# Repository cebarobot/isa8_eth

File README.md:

# ISA 8-Bit Ethernet Controller (THT Version)
ISA 8-Bit Ethernet Network Interface Controller (THT Version)

This is a modified version of [Sergey Kiselev's ISA 8-Bit Ethernet Controller](https://github.com/skiselev/isa8_eth), where surface-mount (SMD) components, except for the RTL8019AS, have been replaced with through-hole (THT) components.

## Changes
* Surface-mount (SMD) components, except for the RTL8019AS, have been replaced with through-hole (THT) components.
* Ethernet Jack (Amphenol RJMG1BD3B8K1ANR) has been replaced by HanRun HR911105A.
* Circuit layout and silkscreen.

## Introduction
ISA 8-Bit Ethernet Controller is an open source network interface controller (NIC) card, designed specifically to be used in computers with 8-bit only ISA (aka XT) bus, such as IBM* PC, IBM* PC XT, various PC/XT compatibles, for example [Micro 8088](https://github.com/skiselev/micro_8088) system. It is based on Realtek RTL8019 ethernet controller and is NE2000-compatible.

## Specifications
* ISA 8-bit interface (62 pin / card edge)
* NE2000 compatible
  * Note: Popular Crynwr NE2000 pocket driver does not support NE2000 in 8-bit slots. Please use the [patched driver](software/driver/) instead
* Supports configuration using switches, jumperless configuration using [RSET8019](software/RSET8019/) utility or PnP
  * Uses DIP switches instead of jumpers for reliability and ease of configuration
* Boot ROM support
  * Socket supports 512 KiB Flash ROM, such as SST/Microchip 39SF040
  * Can be configured in 16 KiB, 32 KiB, 64 KiB, or page mode. In page mode the entire 512 KiB are accessible through a 16 KiB window
  * Also compatible with other DIP 32-pin Flash ROMs, such as 128 KiB 39SF010A, and 256 KiB 39SF020, or similar
  * 40-pin memory extension connector allows connecting up to 4 MiB of memory that can be used in page mode

## Hardware Documentation

### Schematic and PCB Layout

[Schematic - Version THT 1.1](KiCad/ISA8_Ethernet-Schematic-THT-1.1.pdf)

[PCB Layout - Version THT 1.1](KiCad/ISA8_Ethernet-Board-THT-1.1.pdf)

### Building Instructions

#### Assemble the PCB

* Clean the PCB with alcohol
* Apply fluid flux to SMD components pads
* Solder U1 RTL8019 IC
* Solder R1 - R7 resistors and RN1 - RN4 resistor arrays
  * Note that RN1 - RN3 are only required if using DIP switches for configuration. They are not required for jumperless configuration
* Solder C1 - C8 ceramic capacitors
* Solder C9 and C10 tantalum capacitors
* Solder Y1 crystal
* Optional: Program U3 EEPROM. Make sure to use unique MAC address
  * Note: EEPROM can be programmed later using [PG8019](software/PG8019/) utility
* Solder U3 EEPROM
* Optional: Solder SW1 - SW4 DIP switches and U2 IC socket
* Solder J1 Ethernet jack with integrated magentics
* Clean the remaining flux with alcohol

#### Program EEPROM

If EEPROM has not been programmed prior to assembly, now it is a good time to do so.
The U3 EEPROM contains the following configuration for the RTL8019AS chip:
* MAC address
* ISA resources for jumperless configuration
  * Base I/O address
  * IRQ number
  * Boot ROM mode, size, and base memory address
* Other ethernet controller confirguration - medium type, full duplex, LEDs function, power management settings
* Product ID (not normally used, although some vendor specific drivers might check for it)
* Plug and Play data
  * Vendor ID, serial number, PnP version, I/O, memory, and IRQ resources

This information can be programmed using [PG8019](software/PG8019/) utility. The 8019AS.CFG file contains the recommended configuration. Make sure to edit it, and update the MAC address and the serial number. Note that the MAC address is given in the Big-endian format (that is the last byte has the least significant value), while the serial number is given in Little-endian format (that is the first byte has the least significant value). 

A few notes about using PG8019:
* Make sure that your system has 0x300-0x31F I/O addresses available regardless of the Ethernet controller addresses specified in 8019AS.CFG. Note that XT-IDE and XT-CF-Lite frequently use this I/O range. In case you have such a card, you can either temporarily remove it from your system, boot and run PG8019 from a floppy disk, or switch your XT-IDE or XT-CF-Lite to a different address. In the latter case you'll need to update the XT IDE BIOS configuration
* Make sure that your system boots in real mode (no EMM386), or anything else that might interfer with the card. Ideally boot your system without any drivers loaded at all, for example, in later MS-DOS versions it is possible to bypass CONFIG.SYS and AUTOEXEC.BAT by hitting F5 key at the boot time
* After EEPROM has been programmed successfully, the PG8019 utility will print the MAC address, also, it will automatically increment the MAC address and the serial number in 8019AS.CFG, which is useful when programming multiple cards

[Openmoko Inc.](https://github.com/skiselev/openmoko-usb-oui) has generously allocated [00-1F-11-02-60-00 - 00-1F-11-02-7F-FF](https://github.com/skiselev/openmoko-usb-oui/blob/master/ieee_oui.psv) MAC addresses range for ISA 8-Bit Ethernet controller project. You can use MAC addresses from this range for your build, as long as you are using this design. Please apply for a different range if you're redesigning the board or re-using this Ethernet controller design in your own project. I ask you not to use 00-1F-11-02-60-00 - 00-1F-11-02-63-FF range (first 1024 addresses). I am using this range for the cards that I build.

#### Test Ethernet Controller

* Connect Ethernet cable. Make sure that the green "Link" LED lights up
* Use mTCP to test the controller
  * DHCP to obtain IP address
  * FTP or HTGET to download a file

### Switches and Connectors

#### SW1 - CONFIG
This switch block sets the configuration mode

Configuration Mode    | Switch Position
--------------------- | ------------------------
Jumperless / RSET8019 | SW1.1 = OFF, SW1.2 = OFF
Switches              | SW1.1 = ON, SW1.2 = OFF
PnP                   | SW1.1 = OFF, SW1.2 = ON

#### SW2 - IRQ
This switch block, when the card is in the **Switches** configuration mode, sets the Ethernet controller IRQ

IRQ                             | Switch Position
------------------------------- | ------------------------
IRQ2 (on PC/XT) or IRQ9 (on AT) | SW2.1 = OFF, SW2.2 = OFF
IRQ3                            | SW2.1 = ON, SW2.2 = OFF
IRQ4                            | SW2.1 = OFF, SW2.2 = ON
IRQ5                            | SW2.1 = ON, SW2.2 = ON

#### SW3 - IO_ADDR
This switch block, when the card is in the **Switches** configuration mode, sets the Ethernet controller I/O address

I/O Address | SW3.1 | SW3.2 | SW3.3 | SW3.4
----------- | ----- | ----- | ------| -----
0x200       | OFF   | OFF   | ON    | OFF
0x220       | ON    | OFF   | ON    | OFF
0x240       | OFF   | ON    | ON    | OFF
0x260       | ON    | ON    | ON    | OFF
0x280       | OFF   | OFF   | ON    | ON
0x2A0       | ON    | OFF   | ON    | ON
0x2C0       | OFF   | ON    | ON    | ON
0x2E0       | ON    | ON    | ON    | ON
0x300       | OFF   | OFF   | OFF   | OFF
0x320       | ON    | OFF   | OFF   | OFF
0x340       | OFF   | ON    | OFF   | OFF
0x360       | ON    | ON    | OFF   | OFF
0x380       | OFF   | OFF   | OFF   | ON
0x3A0       | ON    | OFF   | OFF   | ON
0x3C0       | OFF   | ON    | OFF   | ON
0x3E0       | ON    | ON    | OFF   | ON

#### SW4 - ROM_ADDR
This switch block, when the card is in the **Switches** configuration mode, sets the Ethernet controller boot ROM address and size

ROM Address  | ROM Size           | SW4.1 | SW4.2 | SW4.3 | SW4.4 | SW4.5
------------ | ------------------ | ----- | ------| ----- | ----- | -----
ROM Disabled | Not applicable     | *     | *     | *     | OFF   | OFF
0xC0000      | 16 KiB             | OFF   | OFF   | OFF   | OFF   | ON
0xC4000      | 16 KiB             | ON    | OFF   | OFF   | OFF   | ON
0xC8000      | 16 KiB             | OFF   | ON    | OFF   | OFF   | ON
0xCC000      | 16 KiB             | ON    | ON    | OFF   | OFF   | ON
0xD0000      | 16 KiB             | OFF   | OFF   | ON    | OFF   | ON
0xD4000      | 16 KiB             | ON    | OFF   | ON    | OFF   | ON
0xD8000      | 16 KiB             | OFF   | ON    | ON    | OFF   | ON
0xDC000      | 16 KiB             | ON    | ON    | ON    | OFF   | ON
0xC0000      | 32 KiB             | OFF   | OFF   | OFF   | ON    | OFF
0xC8000      | 32 KiB             | ON    | OFF   | OFF   | ON    | OFF
0xD0000      | 32 KiB             | OFF   | ON    | OFF   | ON    | OFF
0xD8000      | 32 KiB             | ON    | ON    | OFF   | ON    | OFF
0xC0000      | 64 KiB             | OFF   | OFF   | ON    | ON    | OFF
0xD0000      | 64 KiB             | ON    | OFF   | ON    | ON    | OFF
0xC0000      | 16 KiB / Page mode | OFF   | OFF   | OFF   | ON    | ON
0xC4000      | 16 KiB / Page mode | ON    | OFF   | OFF   | ON    | ON
0xC8000      | 16 KiB / Page mode | OFF   | ON    | OFF   | ON    | ON
0xCC000      | 16 KiB / Page mode | ON    | ON    | OFF   | ON    | ON
0xD0000      | 16 KiB / Page mode | OFF   | OFF   | ON    | ON    | ON
0xD4000      | 16 KiB / Page mode | ON    | OFF   | ON    | ON    | ON
0xD8000      | 16 KiB / Page mode | OFF   | ON    | ON    | ON    | ON
0xDC000      | 16 KiB / Page mode | ON    | ON    | ON    | ON    | ON

#### J1 - Ethernet Connector

#### J2 - MEM_EXT
This connector can be used to add up to 4 MiB of optional memory (ROM or RAM).
The memory, if larger than 64 KiB, can be accessed using the page mode.

Pin | Description   | Pin | Description
--- | ------------- | --- | -----------
1   | 5V            | 2   | 5V
3   | No connection | 4   | A21
5   | No connection | 6   | A20
7   | No connection | 8   | A19
9   | A18           | 10  | /MEMW
11  | A16           | 12  | A17
13  | A15           | 14  | A14
15  | A12           | 16  | A13
17  | A7            | 18  | A8
19  | A6            | 20  | A9
21  | A5            | 22  | A11
23  | A4            | 24  | /MEMR
25  | A3            | 26  | A10
27  | A2            | 28  | /CS
29  | A1            | 30  | D7
31  | A0            | 32  | D6
33  | D0            | 34  | D5
35  | D1            | 36  | D4
37  | D2            | 38  | D3
39  | GND           | 40  | GND

### Bill of Materials - Version THT 1.1

Component type     | Reference | Description                           | Quantity | Possible sources and notes 
------------------ | --------- | ------------------------------------- | -------- | --------------------------
PCB                |           | ISA 8-bit Ethernet PCB - Version 1.0  | 1        | Order from a PCB manufacturer of your choice using provided Gerber or KiCad files
Integrated Circuit | U1        | Realtek RTL8019AS Ethernet Controller | 1        | Authorized Realtek distributors or Taobao
Integrated Circuit | U2        | SST39SF040 - 512 KiB Flash ROM, 32 pin DIP  | 1  | Optional - Boot ROM. 
Integrated Circuit | U3        | 93C46 - 1 Kbit EEPROM, 8 pin DIP      | 1        | Taobao
Quartz Crystal     | Y1        | 20 MHz, 20pF, HC-49U                  | 1        | Taobao
Ethernet Jack      | J1        | HanRun HR911105A - Ethernet jack with magnetics | 1 | Taobao
DIP Switch         | SW1, SW2  | DIP switch, 2 position, SPST          | 2        | Taobao
DIP Switch         | SW3       | DIP switch, 4 position, SPST          | 1        | Taobao
DIP Switch         | SW4       | DIP switch, 5 position, SPST          | 1        | Taobao
Capacitor          | C1, C2    | 30pF MLCC Capacitor, 5.08 mm pitch    | 2        | Taobao
Capacitor          | C3, C4    | 0.01uF MLCC Capacitor, 5.08 mm pitch  | 2        | Taobao
Capacitor          | C5 - C8   | 0.1uF MLCC Capacitor, 5.08 mm pitch   | 4        | Taobao
Capacitor          | C1, C2    | 22uF Tantalum Capacitor, 2.54 mm pitch| 2        | Taobao
Resistor           | R1        | 200 Ohm Resistor, 1/4W, through hole  | 1        | Taobao
Resistor           | R2, R3    | 470 Ohm Resistor, 1/4W, through hole  | 2        | Taobao
Resistor           | R6        | 27 kOhm Resistor, 1/4W, through hole  | 1        | Taobao
Resistor           | R7        | 1 MOhm Resistor, 1/4W, through hole   | 1        | Taobao
Resistor Array     | RN1 - RN2 | 10kOhm, 9 pin SIP, 8 resistors        | 4        | Taobao
IC Socket          | U2        | 32 pin DIP                            | 1        | Taobao
IC Socket          | U3        | 8 pin DIP                             | 1        | Taobao

## Reference Information

### Realtek RTL8019AS EEPROM Content

The Realtek RTL8019AS uses 93C46 - 1Kbit / 128 bytes EEPROM to store the configuration. The EEPROM is accessed using 16-bit word mode, with data being stored in Big-endian format. This means that the bytes should be swapped when the EEPROM content is accessed on an x86 system.

Address      | Size | Content                                | Default Configuration for ISA 8-Bit Ethernet
-------------|------|----------------------------------------|---------------------------------------------
0x00 - 0x03  | 4    | CONFIG1, CONFIG2, CONFIG3, CONFIG4     |
0x00         | 1    | CONFIG1                                | 0x07
0x01         | 1    | CONFIG2                                | 0x00
0x02         | 1    | CONFIG3                                | 0xD0
0x03         | 1    | CONFIG4                                | 0x01
0x04 - 0x09  | 6    | Ethernet ID (MAC Address)              | 0x00 0x1F 0x11 0x02 0x70 0x00
0x0A - 0x11  | 8    | Product ID                             | 0x49 0x53 0x41 0x38 0x45 0x54 0x48 0x20
0x12 - 0x1A  | 9    | PnP header                             | 
0x12 - 0x15  | 4    | Vendor ID (0-3)                        |  
0x12 - 0x13  | 2    | Vendor ID - compressed ASCII (00000=A) | 0x4A 0x8C - 0 10010=R 10100=T 01100=L
0x14 - 0x15  | 2    | Vendor ID - product number             | 0x80 0x19 - 8019
0x16 - 0x19  | 4    | Serial Number (0-3)                    | 0x00 0x10 0x00 0x00
0x1A         | 1    | Checksum                               | ?
0x1B - 0x7F  | 101  | PnP Resource Data                      | 
0x1B - 0x1D  | 3    | PnP Version Number                     |
0x1B         | 1    | Item byte                              | 0x0A
0x1C         | 1    | PnP Version                            | 0x10
0x1D         | 1    | Vendor Version                         | 0x10
0x1E - 0x3B  | 37   | ANSI Identifier String                 | 
0x1E         | 1    | Item byte                              | 0x82
0x1F         | 1    | Length, bits 7-0                       | 0x24
0x20         | 1    | Length, bits 15-8                      | 0x00
0x21 - 0x44  | 36   | Identifier String                      | "ISA 8-Bit Plug & Play Ethernet Card", 0x00
0x45 - 0x4B  | 7    | Logical Device ID                      |
0x45         | 1    | Item byte                              | 0x16
0x46 - 0x49  | 4    | Logical Device ID 0-3                  | 0x00 0x00 0x80 0x19
0x4A         | 1    | Flag 0                                 | 0x02 (Boot ROM disabled) or 0x03 (Boot ROM enabled)
0x4B         | 1    | Flag 1                                 | 0x00
0x4C - 0x50  | 5    | Compatible Device ID (NE2000 compatible) |
0x4C         | 1    | Item byte                              | 0x1C
0x4D - 0x50  | 4    | Compatible ID                          | 0x41 0xD0 0x80 0xD6
0x51 - 0x58  | 8    | I/O Format                             |
0x51         | 1    | Item byte                              | 0x47
0x52         | 1    | I/O Information                        | 0x00
0x53         | 1    | Minimal I/O base, bits 7-0             | 0x20
0x54         | 1    | Minimal I/O base, bits 15-8            | 0x02
0x55         | 1    | Maximal I/O base, bits 7-0             | 0x80
0x56         | 1    | Maximal I/O base, bits 15-8            | 0x03
0x57         | 1    | Base alignment                         | 0x20
0x58         | 1    | Range length                           | 0x20
0x59 - 0x5C  | 4    | IRQ Format                             |
0x59         | 1    | Item byte                              | 0x23 - Small item name = 0x04 (IRQ), Length = 3
0x5A         | 1    | IRQ mask bits 7-0                      | 0x3C - IRQ 0-7 mask - IRQ5, IRQ4, IRQ3, IRQ2
0x5B         | 1    | IRQ mask bits 15-8                     | 0x02 - IRQ 8-15 mask - IRQ9 (note: IRQ9 is the same as IRQ2, others are not available on an 8-bit slot)
0x5C         | 1    | IRQ information                        | 0x01 - High true edge sensitive
0x5D - 0x6A  | 12   | Memory Format (optional)               | 64 KiB Boot ROM (16 KiB Boot ROM)
0x5D         | 1    | Item byte                              | 0x81
0x5E         | 1    | Length, bits 7-0                       | 0x09
0x5F         | 1    | Length, bits 15-8                      | 0x00
0x60         | 1    | Memory information                     | 0x40
0x61         | 1    | Minimal base, bits 15-8                | 0x00
0x62         | 1    | Minimal base, bits 24-16               | 0x0C
0x63         | 1    | Maximal base, bits 7-0                 | 0x00 (0xC0 for 16 KiB)
0x64         | 1    | Maximal base, bits 15-8                | 0x0D
0x65         | 1    | Base alignment, bits 7-0               | 0x00
0x66         | 1    | Base alignment, bits 15-8              | 0x00 (0x40 for 16 KiB)
0x67         | 1    | Range length bits 15-8                 | 0x00 (0x40 for 16 KiB)
0x68         | 1    | Range length bits 24-16                | 0x01 (0x00 for 16 KiB)
0x69 - 0x6A  | 2    | End Tag                                |
0x6B         | 1    | Item byte                              | 0x79
0x6C         | 1    | Checksum of the resource data          | 0x1F
0x6D-0x7F    | ?    | Unused space                           | 0xFF

## Red Tape

### Licensing

ISA 8-bit Ethernet is an open source hardware project certified by [Open Source Hardware Association](https://www.oshwa.org/), certification UID is [US002001](https://certification.oshwa.org/us002001.html). The hardware design itself, including schematic and PCB layout design files are licensed under the strongly-reciprocal variant of [CERN Open Hardware Licence version 2](license-cern_ohl_s_v2.txt). The NE2000 driver code is licensed under [GNU General Public License v2](license-gpl-2.0.txt). Documentation, including this file, is licensed under the [Creative Commons Attribution-ShareAlike 4.0 International License](license-cc-by-sa-4.0.txt).

KiCad symbols and modules used in this project are available in [my KiCad library](https://github.com/skiselev/my_kicad_library) repository

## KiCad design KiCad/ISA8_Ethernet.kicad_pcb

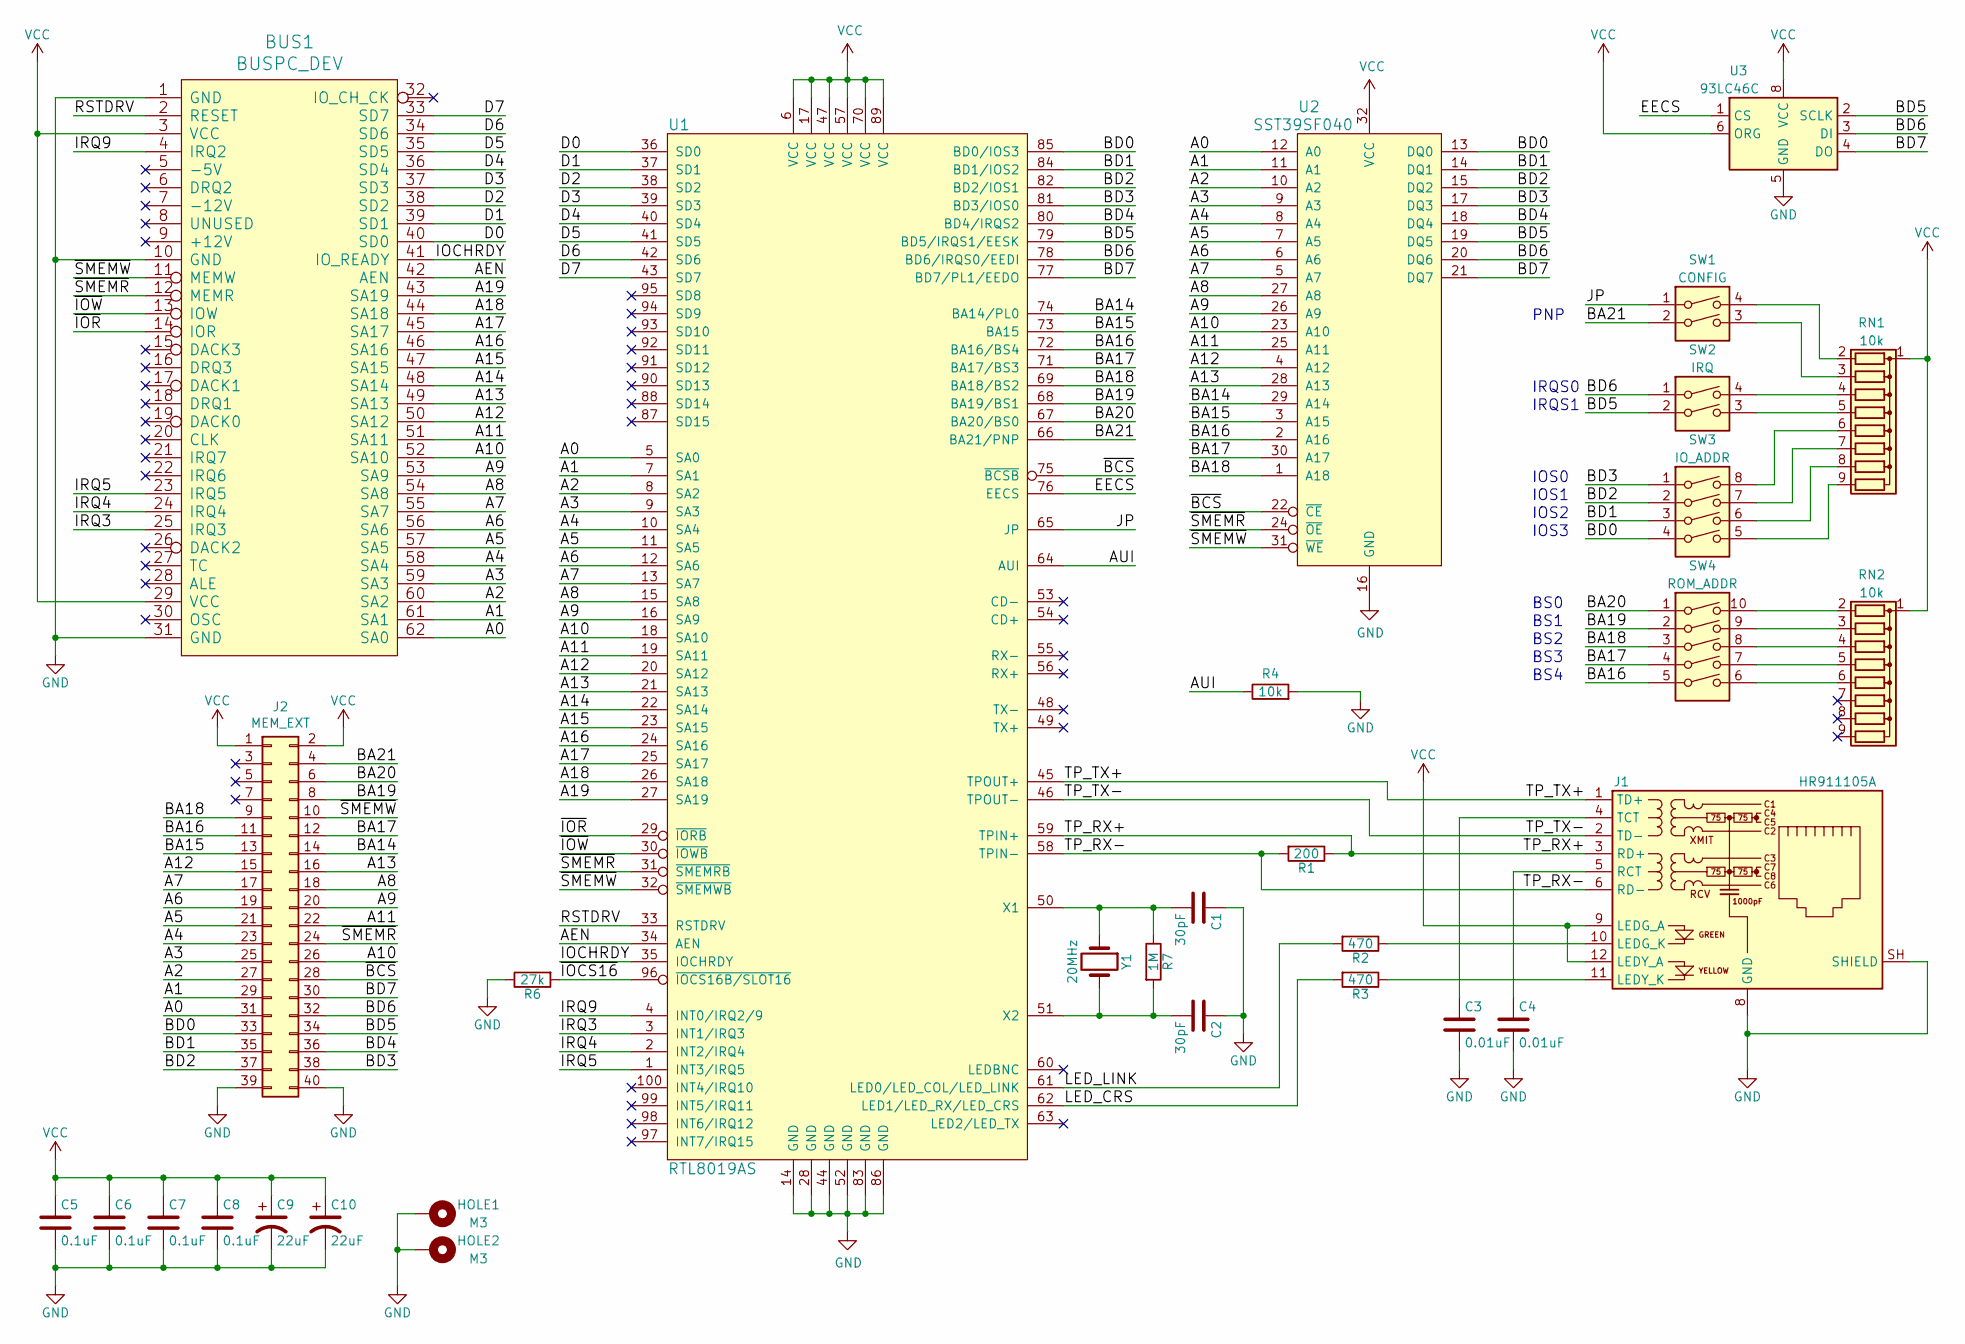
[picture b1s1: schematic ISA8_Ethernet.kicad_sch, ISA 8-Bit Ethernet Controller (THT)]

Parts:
BUS1: BUSPC_DEV; Conn_Edge_PCB_ISA8
C1, C2: 30pF; C_Disc_D7.0mm_W2.5mm_P5.00mm
C3, C4: 0.01uF; C_Disc_D7.0mm_W2.5mm_P5.00mm
C5, C6, C7, C8: 0.1uF; C_Disc_D7.0mm_W2.5mm_P5.00mm
C9, C10: 22uF; CP_Radial_Tantal_D6.0mm_P2.50mm
HOLE1, HOLE2: M3; MountingHole_3.2mm_M3_Pad_Via
J1: HR911105A; RJ45_Hanrun_HR911105A
J2: MEM_EXT; PinHeader_2x20_P2.54mm_Vertical
R1: 200; R_Axial_DIN0207_L6.3mm_D2.5mm_P7.62mm_Horizontal
R2, R3: 470; R_Axial_DIN0207_L6.3mm_D2.5mm_P7.62mm_Horizontal
R4: 10k; R_Axial_DIN0207_L6.3mm_D2.5mm_P7.62mm_Horizontal
R6: 27k; R_Axial_DIN0207_L6.3mm_D2.5mm_P7.62mm_Horizontal
R7: 1M; R_Axial_DIN0207_L6.3mm_D2.5mm_P7.62mm_Horizontal
RN1, RN2: 10k; R_Array_SIP9
SW1: CONFIG; SW_DIP_SPSTx02_Slide_6.7x6.64mm_W7.62mm_P2.54mm_LowProfile
SW2: IRQ; SW_DIP_SPSTx02_Slide_6.7x6.64mm_W7.62mm_P2.54mm_LowProfile
SW3: IO_ADDR; SW_DIP_SPSTx04_Slide_6.7x11.72mm_W7.62mm_P2.54mm_LowProfile
SW4: ROM_ADDR; SW_DIP_SPSTx05_Slide_6.7x14.26mm_W7.62mm_P2.54mm_LowProfile
U1: RTL8019AS; PQFP-100_14x20mm_P0.65mm
U2: SST39SF040; DIP-32_W15.24mm_Socket
U3: 93LC46C; DIP-8_W7.62mm_Socket
Y1: 20MHz; Crystal_HC49-4H_Vertical

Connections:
/A0: BUS1.62 (SA0), J2.31, U1.5 (SA0), U2.12 (A0)
/A1: BUS1.61 (SA1), J2.29, U1.7 (SA1), U2.11 (A1)
/A2: BUS1.60 (SA2), J2.27, U1.8 (SA2), U2.10 (A2)
/A3: BUS1.59 (SA3), J2.25, U1.9 (SA3), U2.9 (A3)
/A4: BUS1.58 (SA4), J2.23, U1.10 (SA4), U2.8 (A4)
/A5: BUS1.57 (SA5), J2.21, U1.11 (SA5), U2.7 (A5)
/A6: BUS1.56 (SA6), J2.19, U1.12 (SA6), U2.6 (A6)
/A7: BUS1.55 (SA7), J2.17, U1.13 (SA7), U2.5 (A7)
/A8: BUS1.54 (SA8), J2.18, U1.15 (SA8), U2.27 (A8)
/A9: BUS1.53 (SA9), J2.20, U1.16 (SA9), U2.26 (A9)
/A10: BUS1.52 (SA10), J2.26, U1.18 (SA10), U2.23 (A10)
/A11: BUS1.51 (SA11), J2.22, U1.19 (SA11), U2.25 (A11)
/A12: BUS1.50 (SA12), J2.15, U1.20 (SA12), U2.4 (A12)
/A13: BUS1.49 (SA13), J2.16, U1.21 (SA13), U2.28 (A13)
/A14: BUS1.48 (SA14), U1.22 (SA14)
/A15: BUS1.47 (SA15), U1.23 (SA15)
/A16: BUS1.46 (SA16), U1.24 (SA16)
/A17: BUS1.45 (SA17), U1.25 (SA17)
/A18: BUS1.44 (SA18), U1.26 (SA18)
/A19: BUS1.43 (SA19), U1.27 (SA19)
/AEN: BUS1.42 (AEN), U1.34 (AEN)
/AUI: R4.1, U1.64 (AUI)
/BA14: J2.14, U1.74 (BA14/PL0), U2.29 (A14)
/BA15: J2.13, U1.73 (BA15), U2.3 (A15)
/BA16: J2.11, SW4.5, U1.72 (BA16/BS4), U2.2 (A16)
/BA17: J2.12, SW4.4, U1.71 (BA17/BS3), U2.30 (A17)
/BA18: J2.9, SW4.3, U1.69 (BA18/BS2), U2.1 (A18)
/BA19: J2.8, SW4.2, U1.68 (BA19/BS1)
/BA20: J2.6, SW4.1, U1.67 (BA20/BS0)
/BA21: J2.4, SW1.2, U1.66 (BA21/PNP)
/BD0: J2.33, SW3.4, U1.85 (BD0/IOS3), U2.13 (DQ0)
/BD1: J2.35, SW3.3, U1.84 (BD1/IOS2), U2.14 (DQ1)
/BD2: J2.37, SW3.2, U1.82 (BD2/IOS1), U2.15 (DQ2)
/BD3: J2.38, SW3.1, U1.81 (BD3/IOS0), U2.17 (DQ3)
/BD4: J2.36, U1.80 (BD4/IRQS2), U2.18 (DQ4)
/BD5: J2.34, SW2.2, U1.79 (BD5/IRQS1/EESK), U2.19 (DQ5), U3.2 (SCLK)
/BD6: J2.32, SW2.1, U1.78 (BD6/IRQS0/EEDI), U2.20 (DQ6), U3.3 (DI)
/BD7: J2.30, U1.77 (BD7/PL1/EEDO), U2.21 (DQ7), U3.4 (DO)
/D0: BUS1.40 (SD0), U1.36 (SD0)
/D1: BUS1.39 (SD1), U1.37 (SD1)
/D2: BUS1.38 (SD2), U1.38 (SD2)
/D3: BUS1.37 (SD3), U1.39 (SD3)
/D4: BUS1.36 (SD4), U1.40 (SD4)
/D5: BUS1.35 (SD5), U1.41 (SD5)
/D6: BUS1.34 (SD6), U1.42 (SD6)
/D7: BUS1.33 (SD7), U1.43 (SD7)
/EECS: U1.76 (EECS), U3.1 (CS)
/IOCHRDY: BUS1.41 (IO_READY), U1.35 (IOCHRDY)
/IRQ3: BUS1.25 (IRQ3), U1.3 (INT1/IRQ3)
/IRQ4: BUS1.24 (IRQ4), U1.2 (INT2/IRQ4)
/IRQ5: BUS1.23 (IRQ5), U1.1 (INT3/IRQ5)
/IRQ9: BUS1.4 (IRQ2), U1.4 (INT0/IRQ2/9)
/JP: SW1.1, U1.65 (JP)
/LED_CRS: R3.2, U1.62 (LED1/LED_RX/LED_CRS)
/LED_LINK: R2.2, U1.61 (LED0/LED_COL/LED_LINK)
/RSTDRV: BUS1.2 (RESET), U1.33 (RSTDRV)
/TP_RX+: J1.3 (RD+), R1.1, U1.59 (TPIN+)
/TP_RX-: J1.6 (RD-), R1.2, U1.58 (TPIN-)
/TP_TX+: J1.1 (TD+), U1.45 (TPOUT+)
/TP_TX-: J1.2 (TD-), U1.46 (TPOUT-)
/~BCS: J2.28, U1.75 (~BCSB), U2.22 (~CE)
/~IOCS16: R6.2, U1.96 (~IOCS16B/SLOT16)
/~IOR: BUS1.14 (IOR), U1.29 (~IORB)
/~IOW: BUS1.13 (IOW), U1.30 (~IOWB)
/~SMEMR: BUS1.12 (MEMR), J2.24, U1.31 (~SMEMRB), U2.24 (~OE)
/~SMEMW: BUS1.11 (MEMW), J2.10, U1.32 (~SMEMWB), U2.31 (~WE)
GND: BUS1.1 (GND), BUS1.10 (GND), BUS1.31 (GND), C1.1, C2.1, C3.2, C4.2, C5.2, C6.2, C7.2, C8.2, C9.2, C10.2, HOLE1.1, HOLE2.1, J1.8 (GND), J1.SH (SHIELD), J2.39, J2.40, R4.2, R6.1, U1.14 (GND), U1.28 (GND), U1.44 (GND), U1.52 (GND), U1.83 (GND), U1.86 (GND), U2.16 (GND), U3.5 (GND)
unnamed: J1.10 (LEDG_K), R2.1
unnamed: J1.11 (LEDY_K), R3.1
unnamed: C4.1, J1.5 (RCT)
unnamed: C3.1, J1.4 (TCT)
unnamed: RN1.2 (R1), SW1.4
unnamed: RN1.3 (R2), SW1.3
unnamed: RN1.4 (R3), SW2.4
unnamed: RN1.5 (R4), SW2.3
unnamed: RN1.6 (R5), SW3.8
unnamed: RN1.7 (R6), SW3.7
unnamed: RN1.8 (R7), SW3.6
unnamed: RN1.9 (R8), SW3.5
unnamed: RN2.2 (R1), SW4.10
unnamed: RN2.3 (R2), SW4.9
unnamed: RN2.4 (R3), SW4.8
unnamed: RN2.5 (R4), SW4.7
unnamed: RN2.6 (R5), SW4.6
unnamed: C1.2, R7.1, U1.50 (X1), Y1.1
unnamed: C2.2, R7.2, U1.51 (X2), Y1.2
VCC: BUS1.3 (VCC), BUS1.29 (VCC), C5.1, C6.1, C7.1, C8.1, C9.1, C10.1, J1.9 (LEDG_A), J1.12 (LEDY_A), J2.1, J2.2, RN1.1 (common), RN2.1 (common), U1.6 (VCC), U1.17 (VCC), U1.47 (VCC), U1.57 (VCC), U1.70 (VCC), U1.89 (VCC), U2.32 (VCC), U3.6 (ORG), U3.8 (VCC)

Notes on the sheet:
BS1
IRQS0
BS4
IOS2
IRQS1
BS3
IOS1
BS0
IOS3
PNP
IOS0
BS2

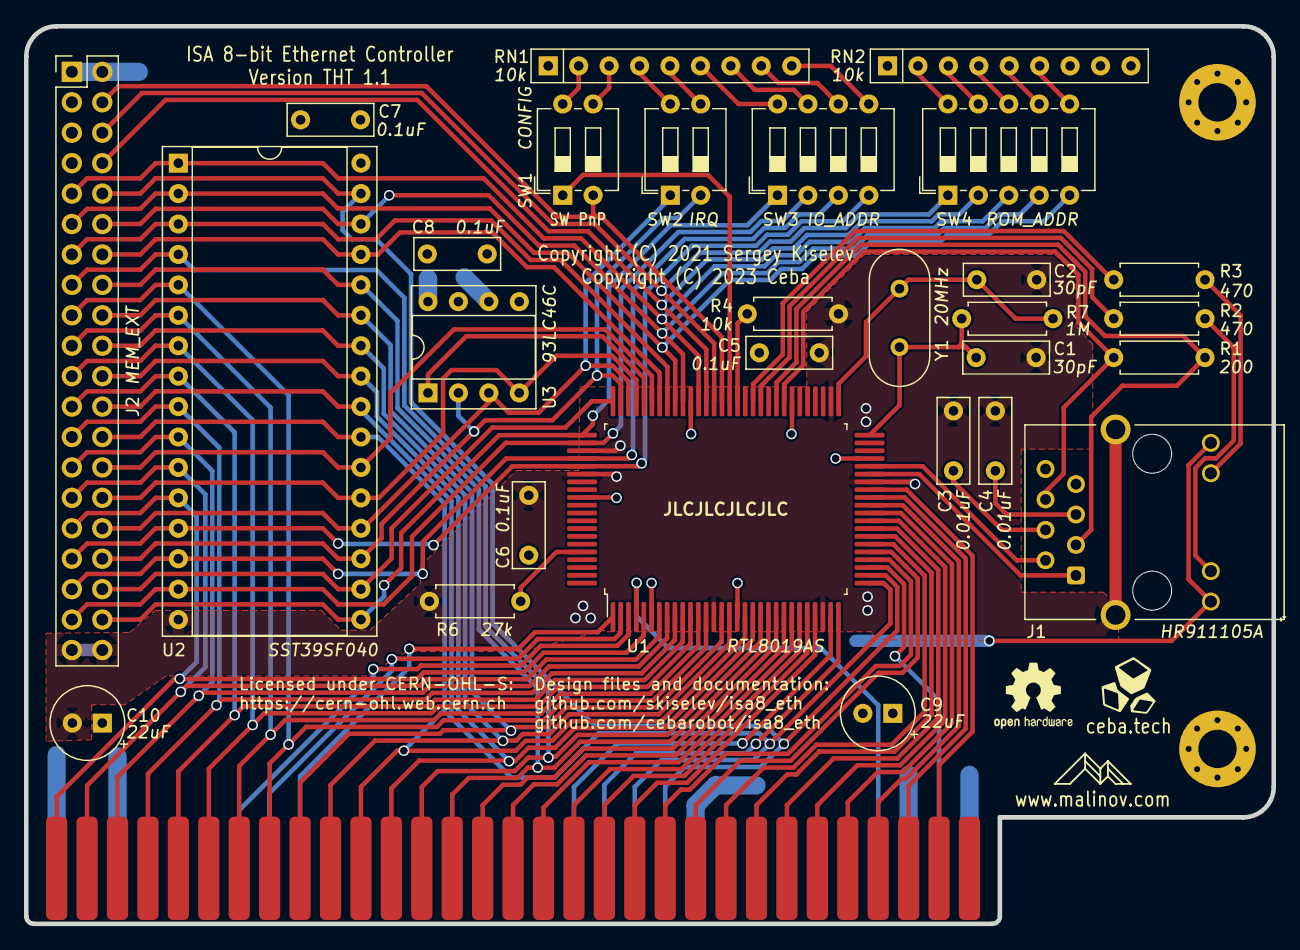
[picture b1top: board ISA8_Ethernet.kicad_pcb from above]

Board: 2 copper layers, 104.1 x 74.9 mm, 31 parts (0 on the bottom side), 87 nets.

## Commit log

2023-05-28 modify board design for THT components
2023-05-28 Update README for THT Version
2023-05-28 Add a new photo

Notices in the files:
README.md:
Licensing:
ISA 8-bit Ethernet is an open source hardware project certified by [Open Source Hardware Association](https://www.oshwa.org/), certification UID is [US002001](https://certification.oshwa.org/us002001.html). The hardware design itself, including schematic and PCB layout design files are licensed under the strongly-reciprocal variant of [CERN Open Hardware Licence version 2](license-cern_ohl_s_v2.txt). The NE2000 driver code is licensed under [GNU General Public License v2](license-gpl-2.0.txt). Documentation, including this file, is licensed under the [Creative Commons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
